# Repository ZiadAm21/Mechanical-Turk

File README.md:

img width="771" alt="PCB-Layout" src="https://github.com/ZiadAm21/Mechanical-Turk/assets/85026466/294146c9-6c39-458a-bf5e-eeac2324a76a"
img width="1029" alt="PCB-3D" src="https://github.com/ZiadAm21/Mechanical-Turk/assets/85026466/c324dfcb-7858-4109-8abc-ef0bd6ab6ac7"

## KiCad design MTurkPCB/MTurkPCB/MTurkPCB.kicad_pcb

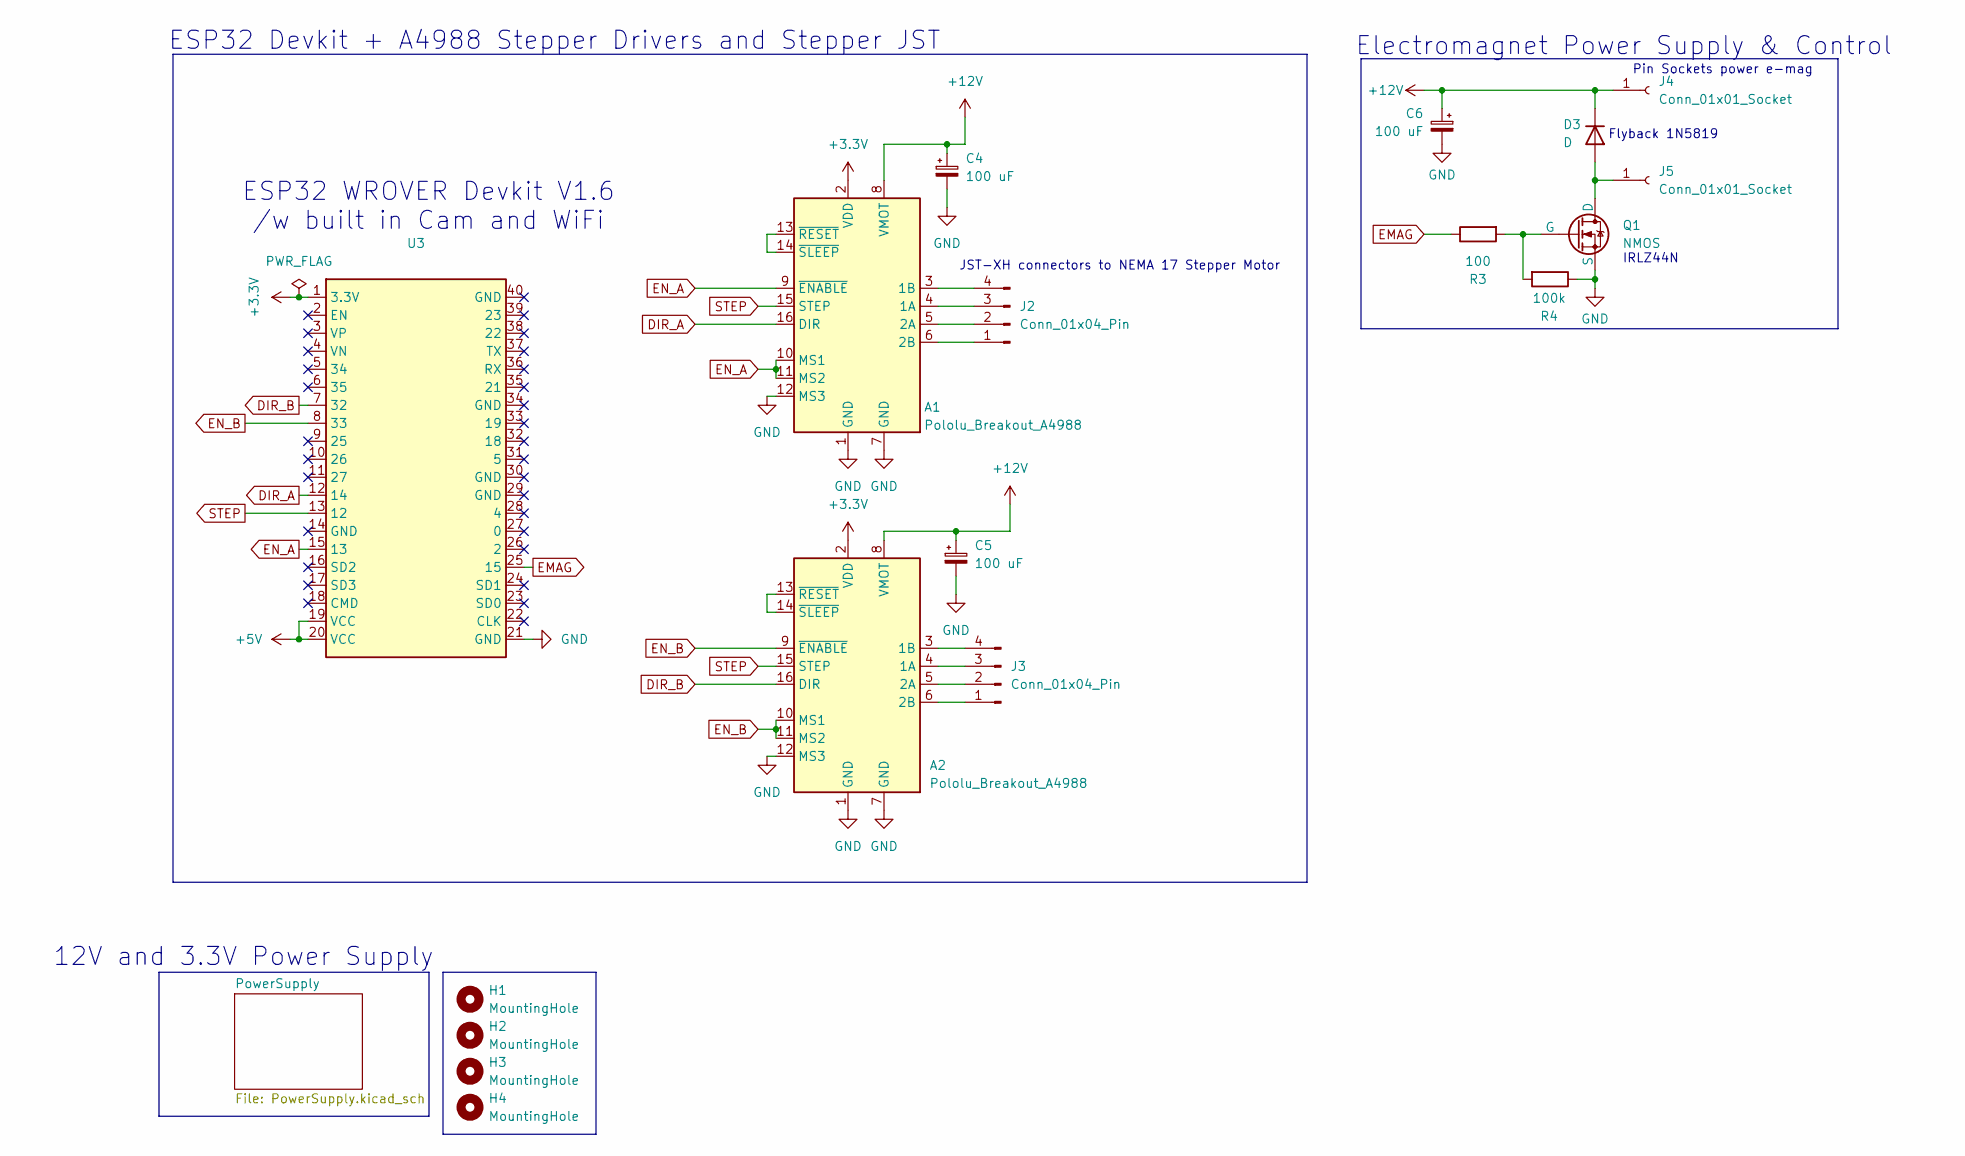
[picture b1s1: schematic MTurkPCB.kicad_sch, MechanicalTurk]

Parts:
A1, A2: Pololu_Breakout_A4988; Pololu_Breakout-16_15.2x20.3mm
C4, C5: 100 uF; C_0603_1608Metric
C6: 100 uF; C_0805_2012Metric_Pad1.18x1.45mm_HandSolder
D3: D; D_DO-41_SOD81_P10.16mm_Horizontal
H1, H2, H3, H4: MountingHole; MountingHole_2.2mm_M2
J2, J3: Conn_01x04_Pin; JST_XH_B4B-XH-A_1x04_P2.50mm_Vertical
J4, J5: Conn_01x01_Socket; PinSocket_1x01_P1.27mm_Vertical
Q1: NMOS; TO-220-3_Vertical
R3: 100; R_0805_2012Metric_Pad1.20x1.40mm_HandSolder
R4: 100k; R_0805_2012Metric_Pad1.20x1.40mm_HandSolder
U3: ESP32 WROVER DevKit V1.6

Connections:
+3.3V: A1.2 (VDD), A2.2 (VDD), U3.1 (3.3V)
+5V: U3.19 (VCC), U3.20 (VCC); also elsewhere on the board
+12V: A1.8 (VMOT), A2.8 (VMOT), C4.1, C5.1, C6.1, D3.1 (K), J4.1; also elsewhere on the board
DIR_A: A1.16 (DIR), U3.12 (14)
DIR_B: A2.16 (DIR), U3.7 (32)
EMAG: R3.1, U3.25 (15)
EN_A: A1.9 (~ENABLE), A1.10 (MS1), A1.11 (MS2), U3.15 (13)
EN_B: A2.9 (~ENABLE), A2.10 (MS1), A2.11 (MS2), U3.8 (33)
GND: A1.1 (GND), A1.7 (GND), A1.12 (MS3), A2.1 (GND), A2.7 (GND), A2.12 (MS3), C4.2, C5.2, C6.2, Q1.3 (S), R4.1, U3.21 (GND); also elsewhere on the board
unnamed: A1.4 (1A), J2.3
unnamed: A1.3 (1B), J2.4
unnamed: A1.5 (2A), J2.2
unnamed: A1.6 (2B), J2.1
unnamed: A1.13 (~RESET), A1.14 (~SLEEP)
unnamed: A2.4 (1A), J3.3
unnamed: A2.3 (1B), J3.4
unnamed: A2.5 (2A), J3.2
unnamed: A2.6 (2B), J3.1
unnamed: A2.13 (~RESET), A2.14 (~SLEEP)
unnamed: D3.2 (A), J5.1, Q1.1 (D)
unnamed: Q1.2 (G), R3.2, R4.2
STEP: A1.15 (STEP), A2.15 (STEP), U3.13 (12)

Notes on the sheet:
ESP32 WROVER Devkit V1.6 /w built in Cam and WiFi
Flyback 1N5819
ESP32 Devkit + A4988 Stepper Drivers and Stepper JST
Electromagnet Power Supply & Control
IRLZ44N
12V and 3.3V Power Supply
Pin Sockets power e-mag
JST-XH connectors to NEMA 17 Stepper Motor

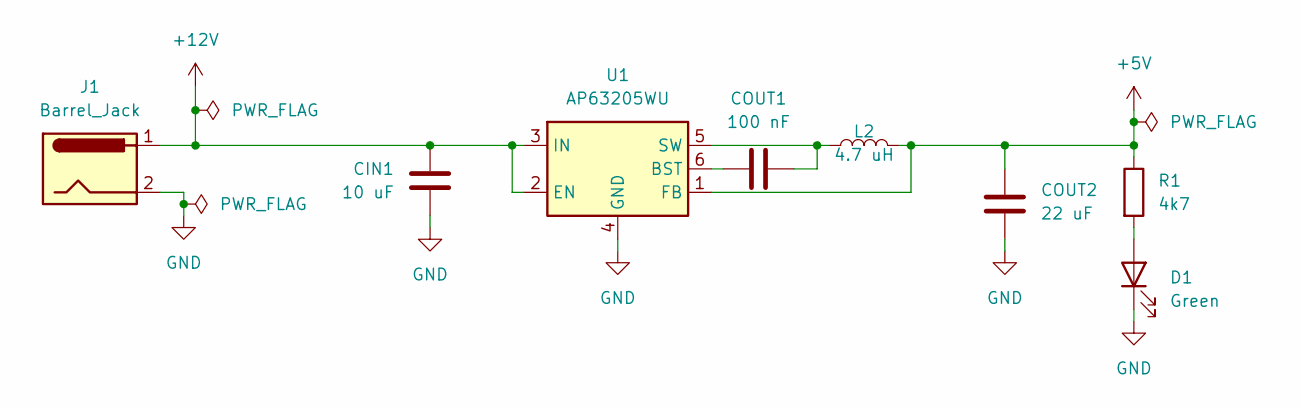
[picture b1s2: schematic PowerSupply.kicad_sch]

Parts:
CIN1: 10 uF; C_0603_1608Metric
COUT1: 100 nF; C_0402_1005Metric
COUT2: 22 uF; C_0805_2012Metric_Pad1.18x1.45mm_HandSolder
D1: Green; LED_0805_2012Metric
J1: Barrel_Jack; BarrelJack_GCT_DCJ200-10-A_Horizontal
L2: 4.7 uH; L_1206_3216Metric
R1: 4k7; R_0805_2012Metric
U1: AP63205WU; TSOT-23-6

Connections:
+5V: COUT2.1, L2.2, R1.1, U1.1 (FB); also elsewhere on the board
+12V: CIN1.1, J1.1, U1.2 (EN), U1.3 (IN); also elsewhere on the board
GND: CIN1.2, COUT2.2, D1.1 (K), J1.2, U1.4 (GND); also elsewhere on the board
unnamed: D1.2 (A), R1.2
unnamed: COUT1.1, U1.6 (BST)
unnamed: COUT1.2, L2.1, U1.5 (SW)

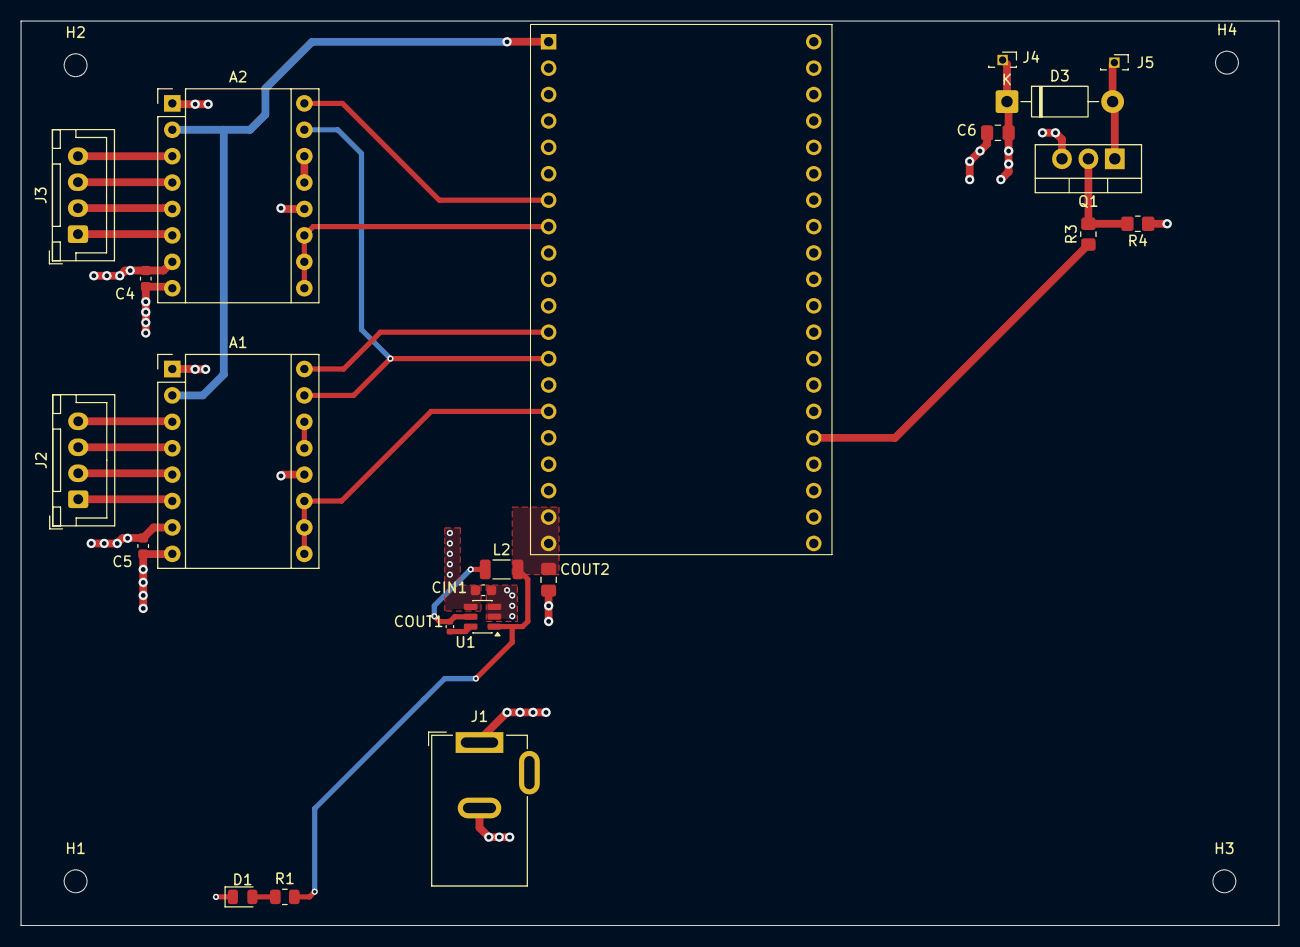
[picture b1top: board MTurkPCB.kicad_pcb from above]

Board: 4 copper layers, 121.0 x 87.0 mm, 26 parts (0 on the bottom side), 25 nets.

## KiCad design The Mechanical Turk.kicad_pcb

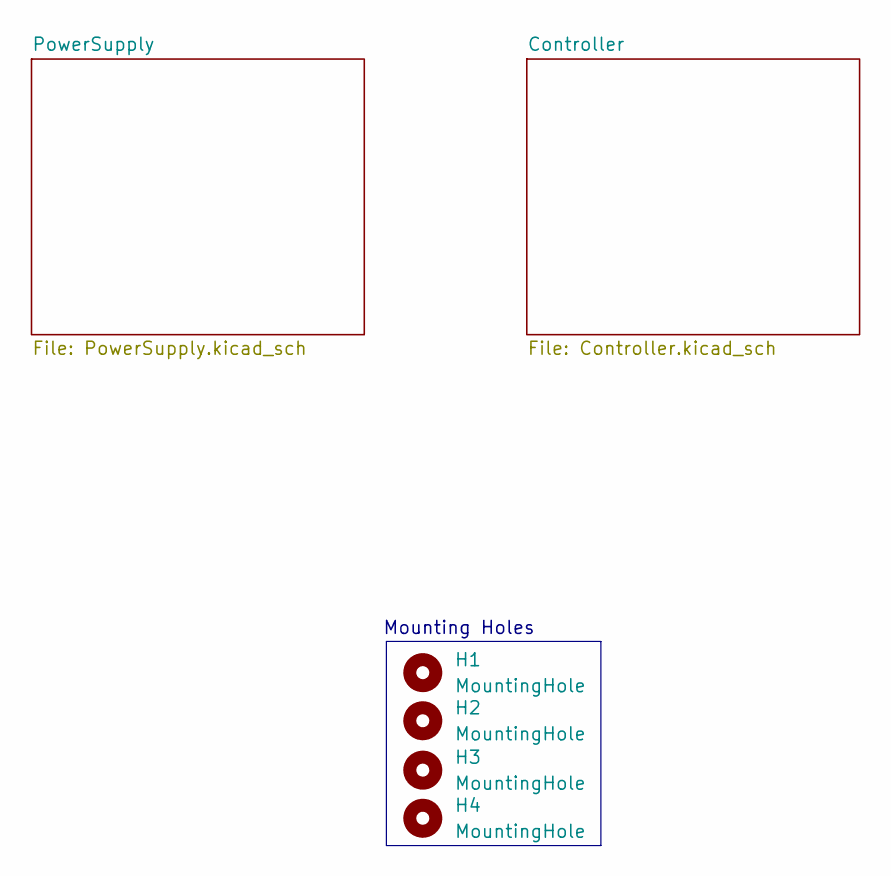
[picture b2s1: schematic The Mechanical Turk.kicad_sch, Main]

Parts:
H1, H2, H3, H4: MountingHole; MountingHole_2.1mm

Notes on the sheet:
Mounting Holes

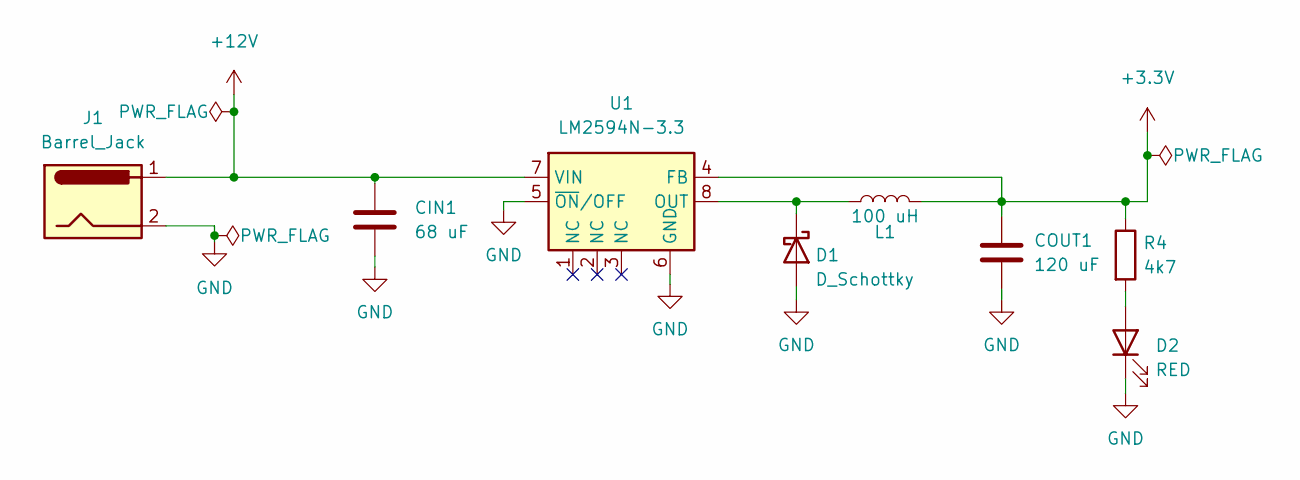
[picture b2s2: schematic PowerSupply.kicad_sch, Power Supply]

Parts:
CIN1: 68 uF; C_3640_9110Metric_Pad2.10x10.45mm_HandSolder
COUT1: 120 uF; C_3640_9110Metric_Pad2.10x10.45mm_HandSolder
D1: D_Schottky; D_3220_8050Metric_Pad2.65x5.15mm_HandSolder
D2: RED; LED_2512_6332Metric_Pad1.52x3.35mm_HandSolder
J1: Barrel_Jack; BarrelJack_CUI_PJ-063AH_Horizontal
L1: 100 uH; L_Axial_L9.5mm_D4.0mm_P2.54mm_Vertical_Fastron_SMCC
R4: 4k7; R_4020_10251Metric_Pad1.65x5.30mm_HandSolder
U1: LM2594N-3.3; DIP-8_W7.62mm

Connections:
+3.3V: COUT1.1, L1.2, R4.1, U1.4 (FB); also elsewhere on the board
+12V: CIN1.1, J1.1, U1.7 (VIN); also elsewhere on the board
GND: CIN1.2, COUT1.2, D1.2 (A), D2.1 (K), J1.2, U1.5 (~ON/OFF), U1.6 (GND); also elsewhere on the board
unnamed: D1.1 (K), L1.1, U1.8 (OUT)
unnamed: D2.2 (A), R4.2

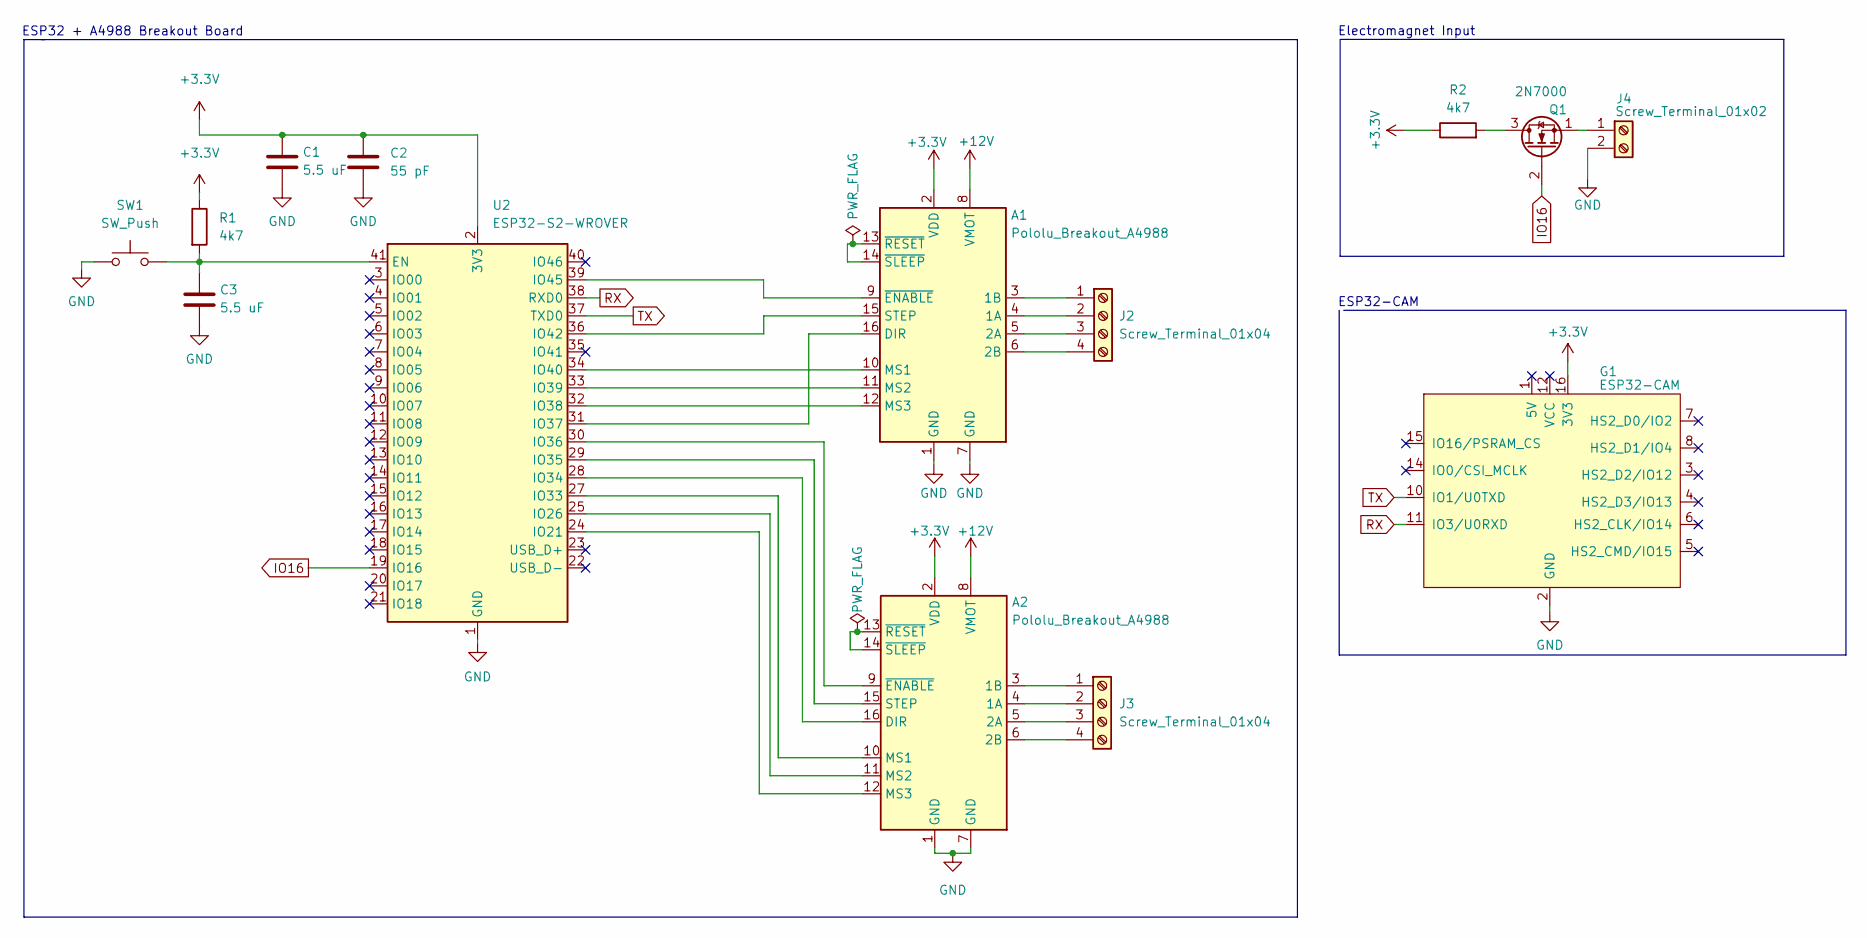
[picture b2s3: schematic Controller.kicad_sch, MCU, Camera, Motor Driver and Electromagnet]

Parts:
A1, A2: Pololu_Breakout_A4988; Pololu_Breakout-16_15.2x20.3mm
C1, C3: 5.5 uF; C_0402_1005Metric_Pad0.74x0.62mm_HandSolder
C2: 55 pF; C_0402_1005Metric_Pad0.74x0.62mm_HandSolder
G1: ESP32-CAM
J2, J3: Screw_Terminal_01x04; PinHeader_1x04_P1.27mm_Vertical
J4: Screw_Terminal_01x02; PinHeader_1x02_P1.27mm_Vertical
Q1: 2N7000; TO-92_Inline
R1, R2: 4k7; R_4020_10251Metric_Pad1.65x5.30mm_HandSolder
SW1: SW_Push; SW_Push_1P1T_NO_6x6mm_H9.5mm
U2: ESP32-S2-WROVER

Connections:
+3.3V: A1.2 (VDD), A2.2 (VDD), C1.1, C2.1, G1.16 (3V3), R1.1, R2.1, U2.2 (3V3); also elsewhere on the board
+12V: A1.8 (VMOT), A2.8 (VMOT); also elsewhere on the board
GND: A1.1 (GND), A1.7 (GND), A2.1 (GND), A2.7 (GND), C1.2, C2.2, C3.2, G1.2 (GND), J4.2, SW1.1, U2.1 (GND), U2.26 (GND), U2.42 (GND), U2.43 (GND); also elsewhere on the board
IO16: Q1.2 (G), U2.19 (IO16)
unnamed: A1.3 (1B), J2.1
unnamed: A1.4 (1A), J2.2
unnamed: A1.5 (2A), J2.3
unnamed: A1.6 (2B), J2.4
unnamed: A1.9 (~ENABLE), U2.39 (IO45)
unnamed: A1.10 (MS1), U2.34 (IO40)
unnamed: A1.11 (MS2), U2.33 (IO39)
unnamed: A1.12 (MS3), U2.32 (IO38)
unnamed: A1.13 (~RESET), A1.14 (~SLEEP)
unnamed: A1.15 (STEP), U2.36 (IO42)
unnamed: A1.16 (DIR), U2.31 (IO37)
unnamed: A2.3 (1B), J3.1
unnamed: A2.4 (1A), J3.2
unnamed: A2.5 (2A), J3.3
unnamed: A2.6 (2B), J3.4
unnamed: A2.9 (~ENABLE), U2.30 (IO36)
unnamed: A2.10 (MS1), U2.27 (IO33)
unnamed: A2.11 (MS2), U2.25 (IO26)
unnamed: A2.12 (MS3), U2.24 (IO21)
unnamed: A2.13 (~RESET), A2.14 (~SLEEP)
unnamed: A2.15 (STEP), U2.29 (IO35)
unnamed: A2.16 (DIR), U2.28 (IO34)
unnamed: C3.1, R1.2, SW1.2, U2.41 (EN)
unnamed: J4.1, Q1.1 (S)
unnamed: Q1.3 (D), R2.2
RX: G1.11 (IO3/U0RXD), U2.38 (RXD0)
TX: G1.10 (IO1/U0TXD), U2.37 (TXD0)

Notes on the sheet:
ESP32 + A4988 Breakout Board
Electromagnet Input
ESP32-CAM

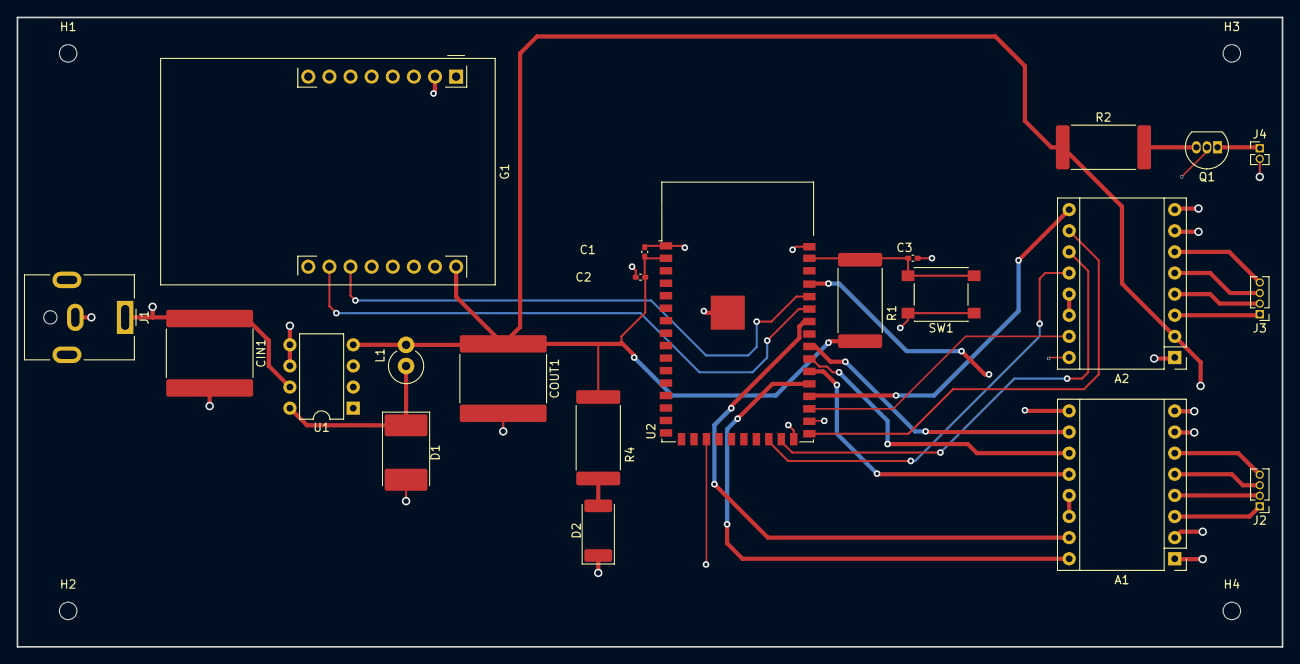
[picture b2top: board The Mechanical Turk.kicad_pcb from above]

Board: 4 copper layers, 152.1 x 75.7 mm, 26 parts (0 on the bottom side), 33 nets.

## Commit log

2024-05-25 removing unnecessary
2026-03-24 Changed Schematics and ESP code
2026-03-24 Add screenshots to README
    Added additional screenshots to the README for better visualization.
